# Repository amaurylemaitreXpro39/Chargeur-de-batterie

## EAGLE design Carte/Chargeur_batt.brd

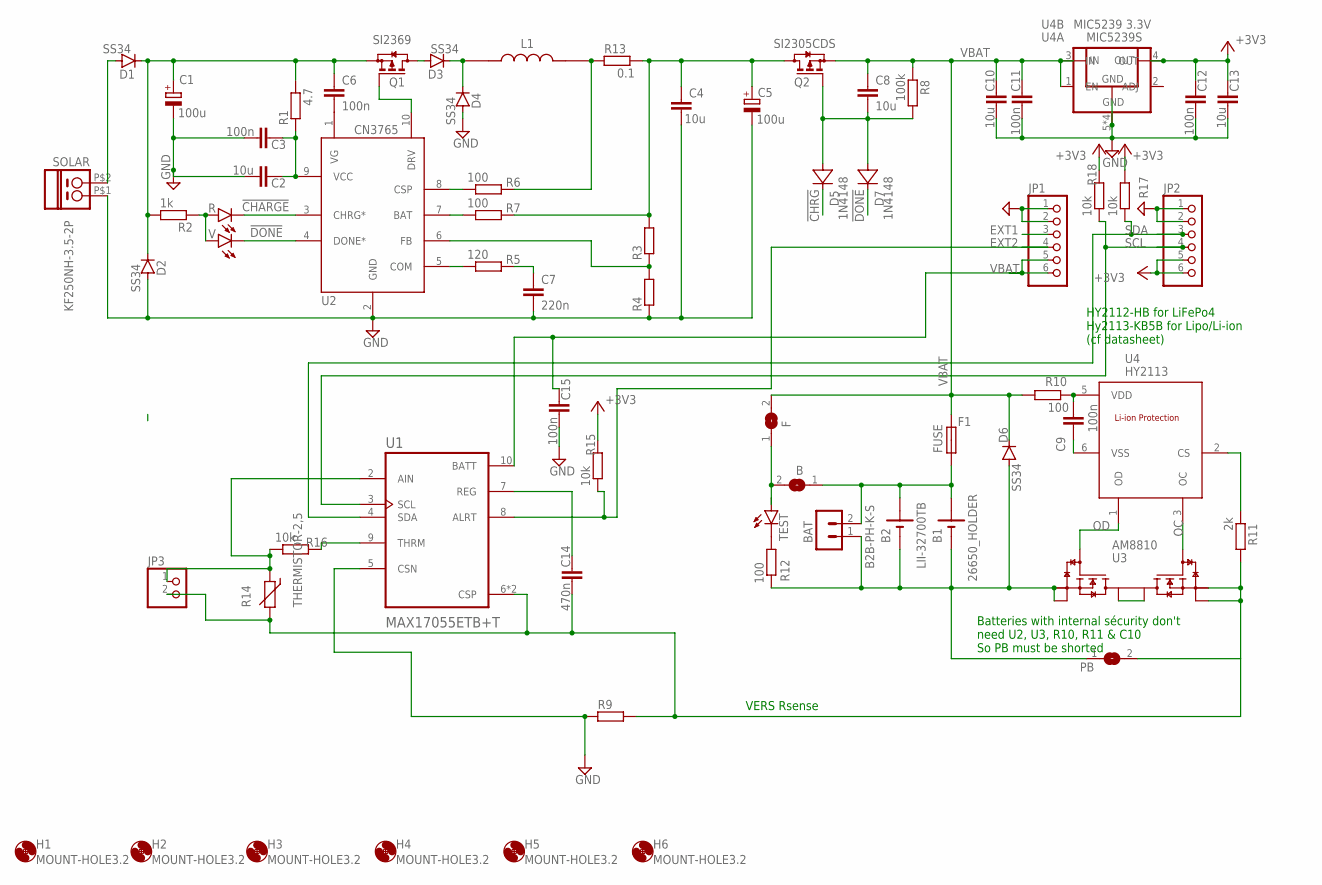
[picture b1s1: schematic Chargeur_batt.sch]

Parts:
B: SJ
B1: 26650_HOLDER; 26650
B2: LII-32700TB
BAT: B2B-PH-K-S
C1, C5: 100u; PANASONIC_D
C2, C4, C8: 10u; C0805K
C3, C6, C9, C15: 100n; C0805K
C7: 220n; C0805K
C10, C13: 10u; C1206
C11, C12: 100n; C1206
C14: 470n; C1206
D1, D2, D3, D4, D6: SS34; DO-214AC
D5, D7: 1N4148; VISHAY_1N4148W-E3-08_0
F: SJ
F1: FUSE; R1206
H1, H2, H3, H4, H5, H6: MOUNT-HOLE3.2; 3,2
JP1, JP2: PINHD-1X6S; 1X06S
JP3: PINHD-1X2; 1X02
L1: IND15; IND_15
PB: SJ
Q1: SI2369; SOT23
Q2: SI2305CDS; SOT23
R: LEDSML0805; SML0805
R1: 4.7; R1206
R2: 1k; R1206
R3, R4: R-EU_R1206; R1206
R5: 120; R1206
R6, R7, R10, R12: 100; R1206
R8: 100k; M1206
R9: R-EU_R2512; R2512
R11: 2k; R1206
R13: 0.1; R2512
R14: THERMISTOR-2,5; RS-2,5
R15, R16, R17, R18: 10k; R1206
SOLAR: KF250NH-3.5-2P
TEST: LEDSML0805; SML0805
U1: MAX17055ETB+T; SON40P200X250X80-11N
U2: CN3765; SSOP
U3: AM8810; TSSOP8
U4: HY2113; SOT23-6
U4A: MIC5239S; SOT223
U4B: MIC5239 3.3V; MSOP08
V: LEDSML0805; SML0805

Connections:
!CHARGE: R.C, U2.3 (CHRG*)
!CHRG: D5.1 (C)
!DONE: D7.1 (C), U2.4 (DONE*), V.C
+3V3: C12.1, C13.1, JP2.5, JP2.6, R15.1, R17.1, R18.1, U4A.3 (OUT), U4B.4 (OUT)
B: B.1, B1.+, B2.+, BAT.2, F1.1
BAT-1: B1.-, B2.-, BAT.1, D6.A, PB.1, R12.2, U3.2 (S1), U3.3 (S1A)
EXT1: JP1.3
EXT2: JP1.4, R15.2, U1.8 (ALRT)
GND: C1.-, C2.2, C3.2, C4.2, C5.-, C7.2, C10.2, C11.2, C12.2, C13.2, C15.2, D2.A, D4.A, JP1.1, JP1.2, JP2.1, JP2.2, R4.1, R9.1, SOLAR.P$1 (1), U1.5 (CSN), U2.2 (GND), U4A.2 (GND), U4A.4 (GND), U4B.5 (GND), U4B.6 (GND), U4B.7 (GND), U4B.8 (GND)
unnamed: C14.2, JP3.2, PB.2, R9.2, R11.2, R14.2, U1.6 (CSP), U1.11 (CSP), U3.6 (S2), U3.7 (S2A)
unnamed: C4.1, C5.+, Q2.3 (D), R3.2, R7.1, R13.2
unnamed: C6.2, U2.1 (VG)
unnamed: D3.A, Q1.3 (D)
unnamed: C2.1, C3.1, R1.1, U2.9 (VCC)
unnamed: C8.2, D5.2 (A), D7.2 (A), Q2.1 (G), R8.2
unnamed: C7.1, R5.1
unnamed: C9.1, R10.2, U4.5 (VDD)
unnamed: U3.1 (D1), U3.8 (D2)
unnamed: R3.1, R4.2, U2.6 (FB)
unnamed: Q1.1 (G), U2.10 (DRV)
unnamed: D3.C, D4.C, L1.1
unnamed: L1.2, R6.1, R13.1
unnamed: D1.A, SOLAR.P$2 (2)
unnamed: R12.1, TEST.C
unnamed: C1.+, C6.1, D1.C, D2.C, Q1.2 (S), R1.2, R2.2
unnamed: R6.2, U2.8 (CSP)
unnamed: R7.2, U2.7 (BAT)
unnamed: R16.1, U1.9 (THRM)
unnamed: R5.2, U2.5 (COM)
unnamed: JP3.1, R14.1, R16.2, U1.2 (AIN)
unnamed: R.A, R2.1, V.A
unnamed: C14.1, U1.7 (REG)
unnamed: R11.1, U4.2 (CS)
unnamed: B.2, F.1, TEST.A
unnamed: C9.2, U4.6 (VSS)
OC: U3.5 (G2), U4.3 (OC)
OD: U3.4 (G1), U4.1 (OD)
SCL: JP2.4, R18.2, U1.3 (SCL)
SDA: JP2.3, R17.2, U1.4 (SDA)
VBAT: C8.1, C10.1, C11.1, C15.1, D6.C, F.2, F1.2, JP1.5, JP1.6, Q2.2 (S), R8.1, R10.1, U1.10 (BATT), U4A.1 (IN), U4B.1 (EN), U4B.3 (IN)

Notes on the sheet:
HY2112-HB for LiFePo4 Hy2113-KB5B for Lipo/Li-ion (cf datasheet)
Batteries with internal sécurity don't need U2, U3, R10, R11 & C10 So PB must be shorted
VERS Rsense

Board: 2 copper layers, 69 parts (2 on the bottom side), 38 nets, no tracks yet.

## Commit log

2025-11-12 Controleurs de charge
2025-11-12 Recap séance
2025-11-27 fuel gauge
2025-11-27 Revert "fuel gauge"
    This reverts commit 6bdba6e3708b8bd39b973b71292792cb5359b32b.
2025-11-27 Try solve push fail
2025-11-27 restore revert commit
2025-11-27 Add fuel gauges
2026-04-10 add recap
2026-04-23 Create EcoConception
2026-04-23 Create ACV
2026-05-13 Create Rapport
2026-05-13 Create ...

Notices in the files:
parts and their libraries:
diy-modules1.8-perso: Released under the Creative Commons Attribution 4.0 International License: http://creativecommons.org/licenses/by/4.0
micrel: Copyright (C) 2008, Bob Starr
